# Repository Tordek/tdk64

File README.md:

TDK64 - a PIC-based USB adapter for N64 game pads
=================================================

You will need [Microchip MLA](https://www.microchip.com/mplab/microchip-libraries-for-applications) for the USB libraries.

The USB VID and PID have been chosen arbitrarily; they might cause conflicts that need to be resolved.

Warning
-------

This is an old project that I haven't updated in a while. `cheat.c` is not included because it's an easter egg that I implemented for my version.

It should work, from the last time I tested it. There is a KiCAD schematic included in the `n64` directory.

Have fun!

License
-------

This project is licensed under GNU GPL v3.0. See LICENSE.md for details.

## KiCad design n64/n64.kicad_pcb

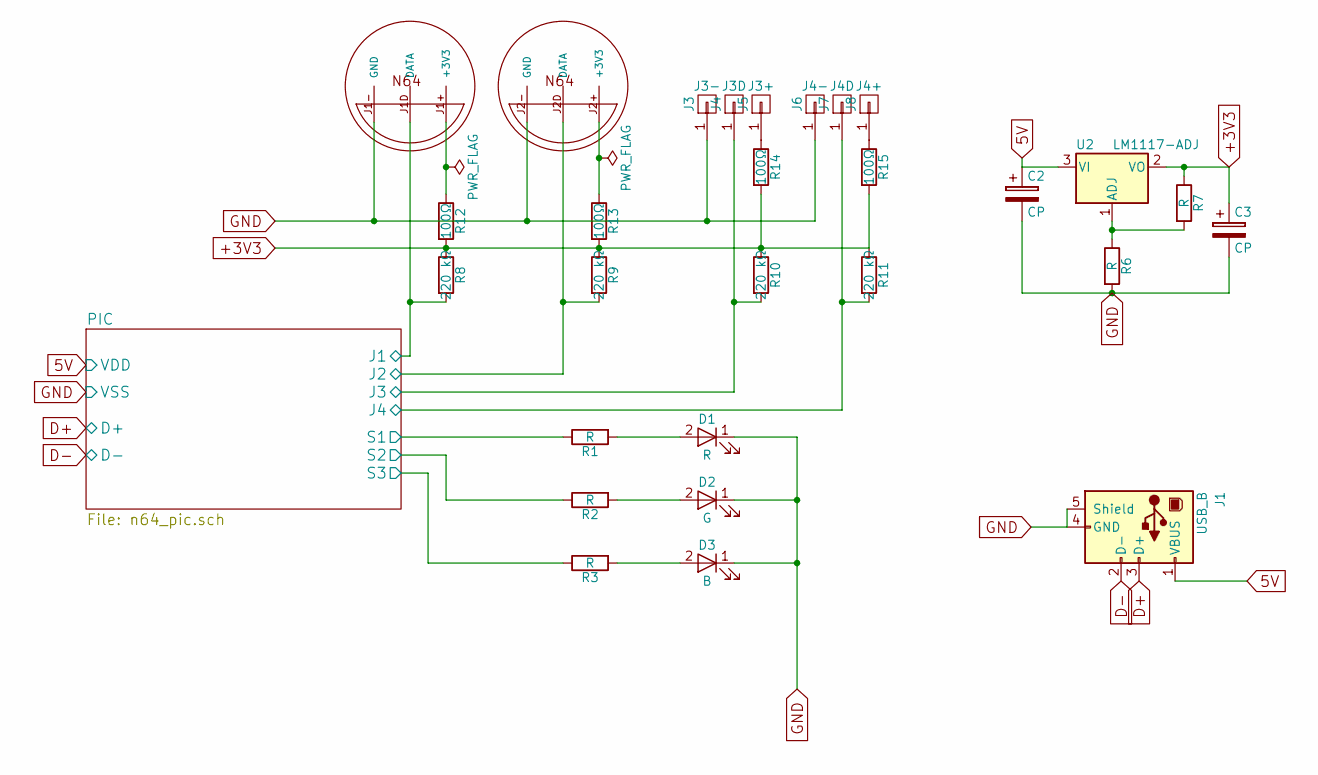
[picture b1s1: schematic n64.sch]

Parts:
C2, C3: CP; CP_Radial_D6.3mm_P2.50mm
D1: R; LED_Rectangular_W5.0mm_H2.0mm
D2: G; LED_Rectangular_W5.0mm_H2.0mm
D3: B; LED_Rectangular_W5.0mm_H2.0mm
J1: USB_B
J3: J3-; Pin_Header_Straight_1x01_Pitch2.54mm
J4: J3D; Pin_Header_Straight_1x01_Pitch2.54mm
J5: J3+; Pin_Header_Straight_1x01_Pitch2.54mm
J6: J4-; Pin_Header_Straight_1x01_Pitch2.54mm
J7: J4D; Pin_Header_Straight_1x01_Pitch2.54mm
J8: J4+; Pin_Header_Straight_1x01_Pitch2.54mm
M1: N64-PORT; n64-N64-DUAL-PORT-LEFT
R1, R2, R3, R6, R7: R; R_0805_HandSoldering
R8, R9, R10, R11: 220 kΩ; R_0805_HandSoldering
R12, R13, R14, R15: 100Ω; R_0805_HandSoldering
U2: LM1117-ADJ; SOT-223-3Lead_TabPin2

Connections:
5V: C2.1, J1.1 (VBUS), U2.3 (VI); also elsewhere on the board
+3V3: C3.1, R7.1, R8.1, R9.1, R10.1, R11.1, R12.2, R13.2, R14.2, R15.2, U2.2 (VO)
/PIC/J1: M1.J1D (DATA), R8.2; also elsewhere on the board
/PIC/J2: M1.J2D (DATA), R9.2; also elsewhere on the board
/PIC/J3: J4.1, R10.2; also elsewhere on the board
/PIC/J4: J7.1, R11.2; also elsewhere on the board
/PIC/S1: R1.1; also elsewhere on the board
/PIC/S2: R2.1; also elsewhere on the board
/PIC/S3: R3.1; also elsewhere on the board
D+: J1.3 (D+); also elsewhere on the board
D-: J1.2 (D-); also elsewhere on the board
GND: C2.2, C3.2, D1.1 (K), D2.1 (K), D3.1 (K), J1.4 (GND), J1.5 (Shield), J3.1, J6.1, M1.J1- (GND), M1.J2- (GND), R6.2; also elsewhere on the board
unnamed: D1.2 (A), R1.2
unnamed: D2.2 (A), R2.2
unnamed: D3.2 (A), R3.2
unnamed: J5.1, R14.1
unnamed: J8.1, R15.1
unnamed: M1.J1+ (+3V3), R12.1
unnamed: M1.J2+ (+3V3), R13.1
unnamed: R6.1, R7.2, U2.1 (ADJ)

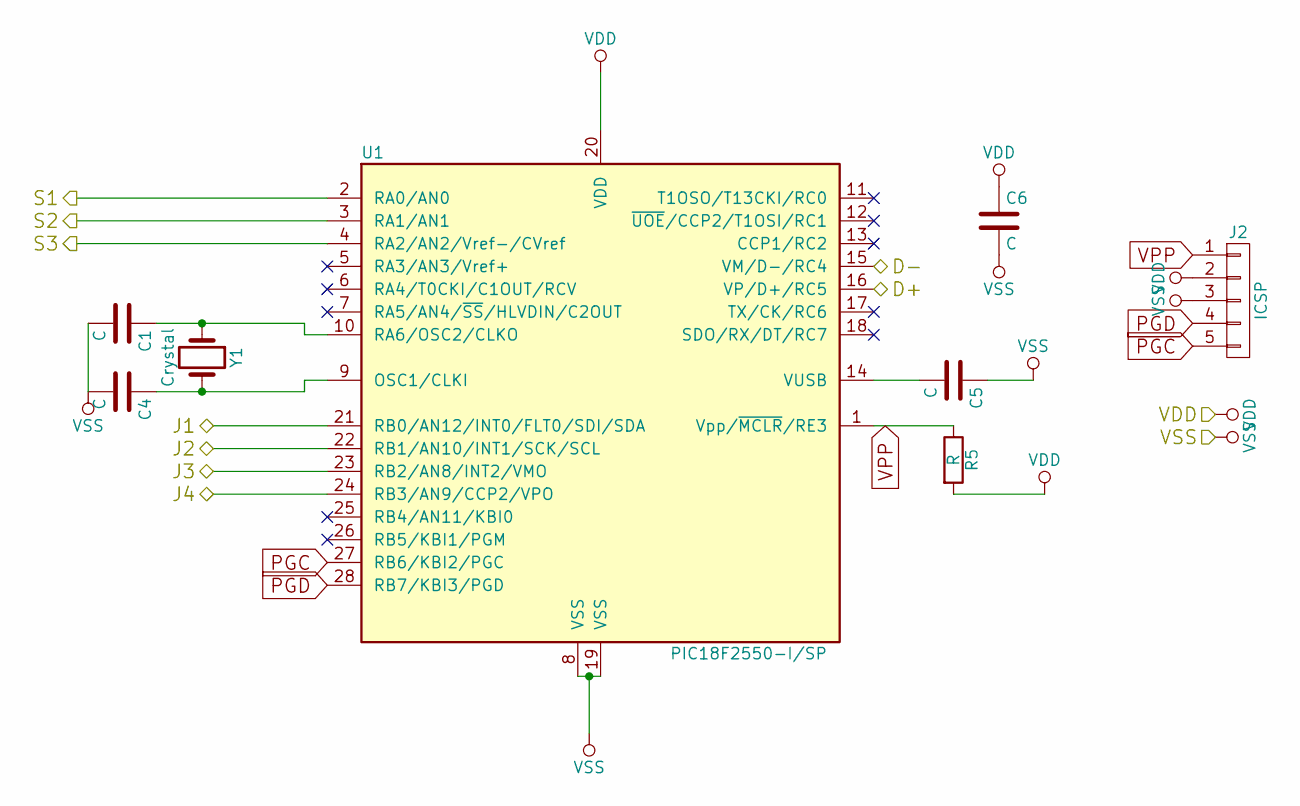
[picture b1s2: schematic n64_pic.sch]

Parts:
C1, C4, C5, C6: C; C_0805_HandSoldering
J2: ICSP; Pin_Header_Straight_1x05_Pitch2.54mm
R5: R; R_0805_HandSoldering
U1: PIC18F2550-I/SP; DIP-28_W7.62mm
Y1: Crystal; Crystal_HC49-4H_Vertical

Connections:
5V: C6.1, J2.2, R5.2, U1.20 (VDD); also elsewhere on the board
/PIC/J1: U1.21 (RB0/AN12/INT0/FLT0/SDI/SDA); also elsewhere on the board
/PIC/J2: U1.22 (RB1/AN10/INT1/SCK/SCL); also elsewhere on the board
/PIC/J3: U1.23 (RB2/AN8/INT2/VMO); also elsewhere on the board
/PIC/J4: U1.24 (RB3/AN9/CCP2/VPO); also elsewhere on the board
/PIC/S1: U1.2 (RA0/AN0); also elsewhere on the board
/PIC/S2: U1.3 (RA1/AN1); also elsewhere on the board
/PIC/S3: U1.4 (RA2/AN2/Vref-/CVref); also elsewhere on the board
D+: U1.16 (VP/D+/RC5); also elsewhere on the board
D-: U1.15 (VM/D-/RC4); also elsewhere on the board
GND: C1.2, C4.2, C5.1, C6.2, J2.3, U1.8 (VSS), U1.19 (VSS); also elsewhere on the board
unnamed: C1.1, U1.10 (RA6/OSC2/CLKO), Y1.1
unnamed: C4.1, U1.9 (OSC1/CLKI), Y1.2
unnamed: C5.2, U1.14 (VUSB)
PGC: J2.5, U1.27 (RB6/KBI2/PGC)
PGD: J2.4, U1.28 (RB7/KBI3/PGD)
VPP: J2.1, R5.1, U1.1 (Vpp/~MCLR~/RE3)

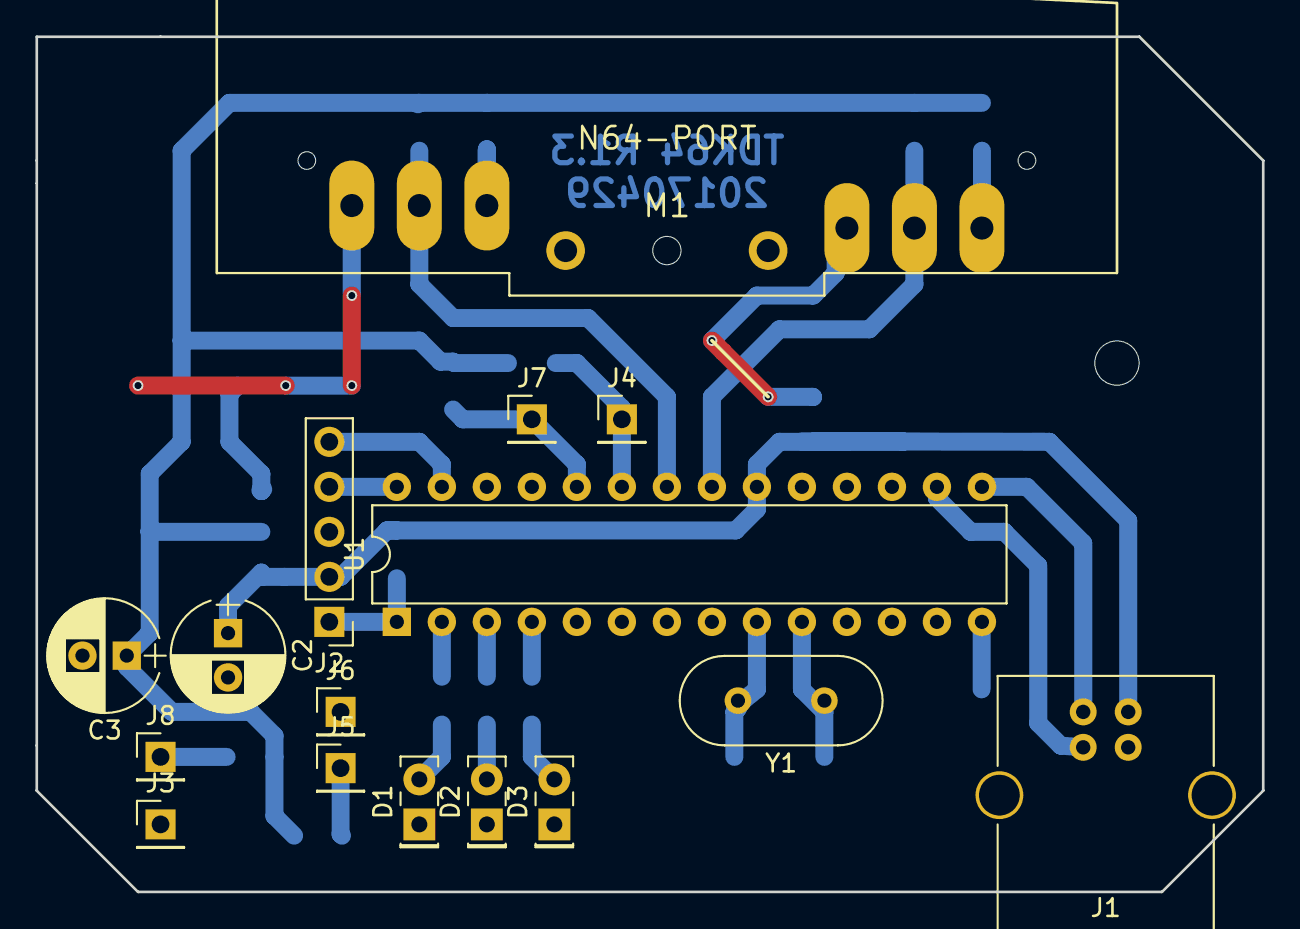
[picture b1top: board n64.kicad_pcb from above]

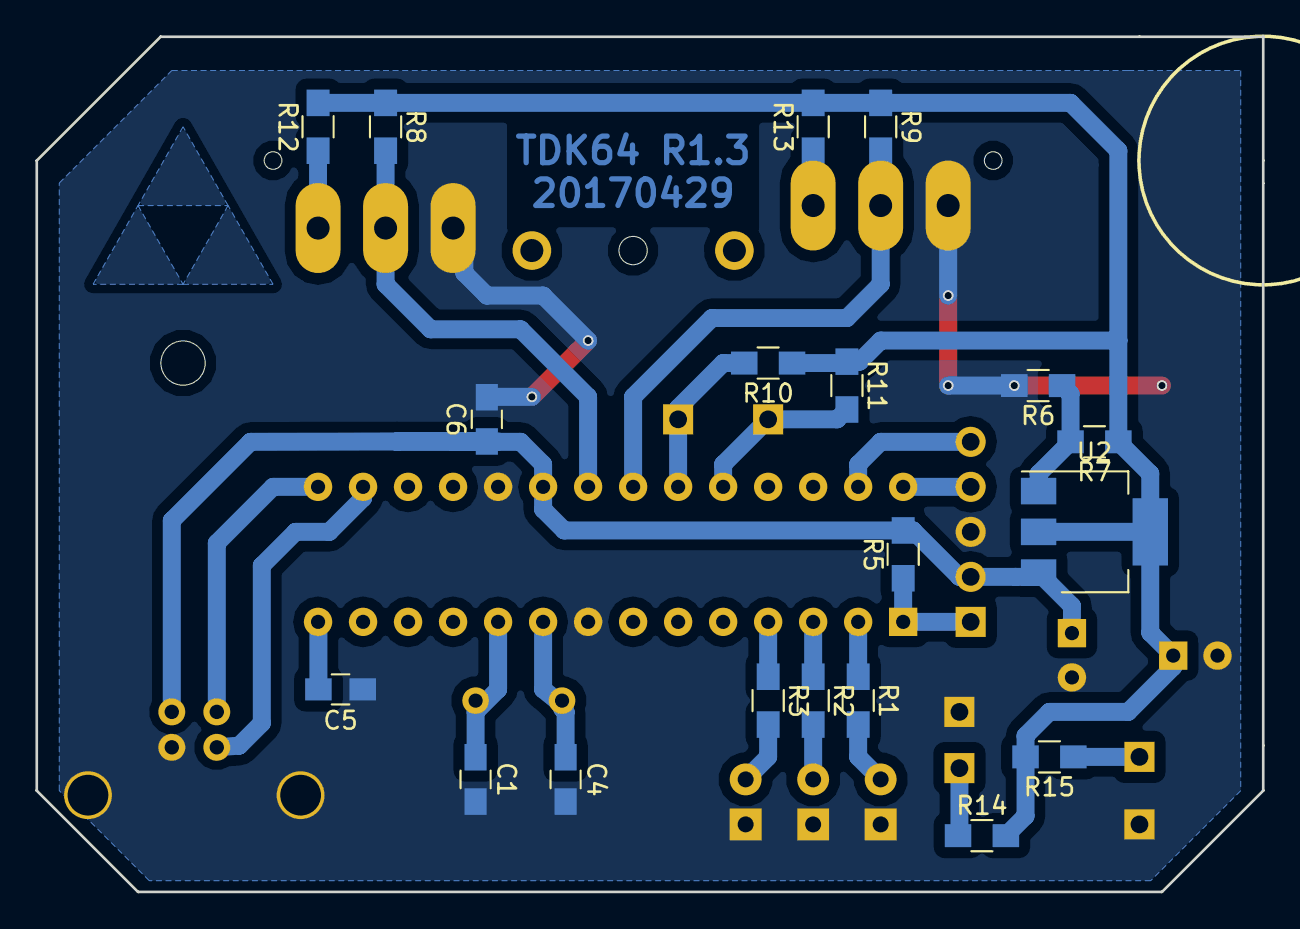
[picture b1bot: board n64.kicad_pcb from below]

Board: 2 copper layers, 69.2 x 48.3 mm, 35 parts (19 on the bottom side), 26 nets.

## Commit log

2020-08-02 First commit.
2020-08-02 Initial version, latest working.
    Unfortunately had to clear out the repo because I commited some unwanted files.
2020-08-02 Add Warning to README.
2020-08-02 Create LICENSE
2020-08-02 Update README for clarifications on building.
